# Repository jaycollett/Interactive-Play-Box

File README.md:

# Interactive-Play-Box
Arduino controlled box with buttons, keypads, switches and fun things for kids to poke, push and flip.

Custom Arduino-clone board used to control a box I built for my son for his 4th Christmas.

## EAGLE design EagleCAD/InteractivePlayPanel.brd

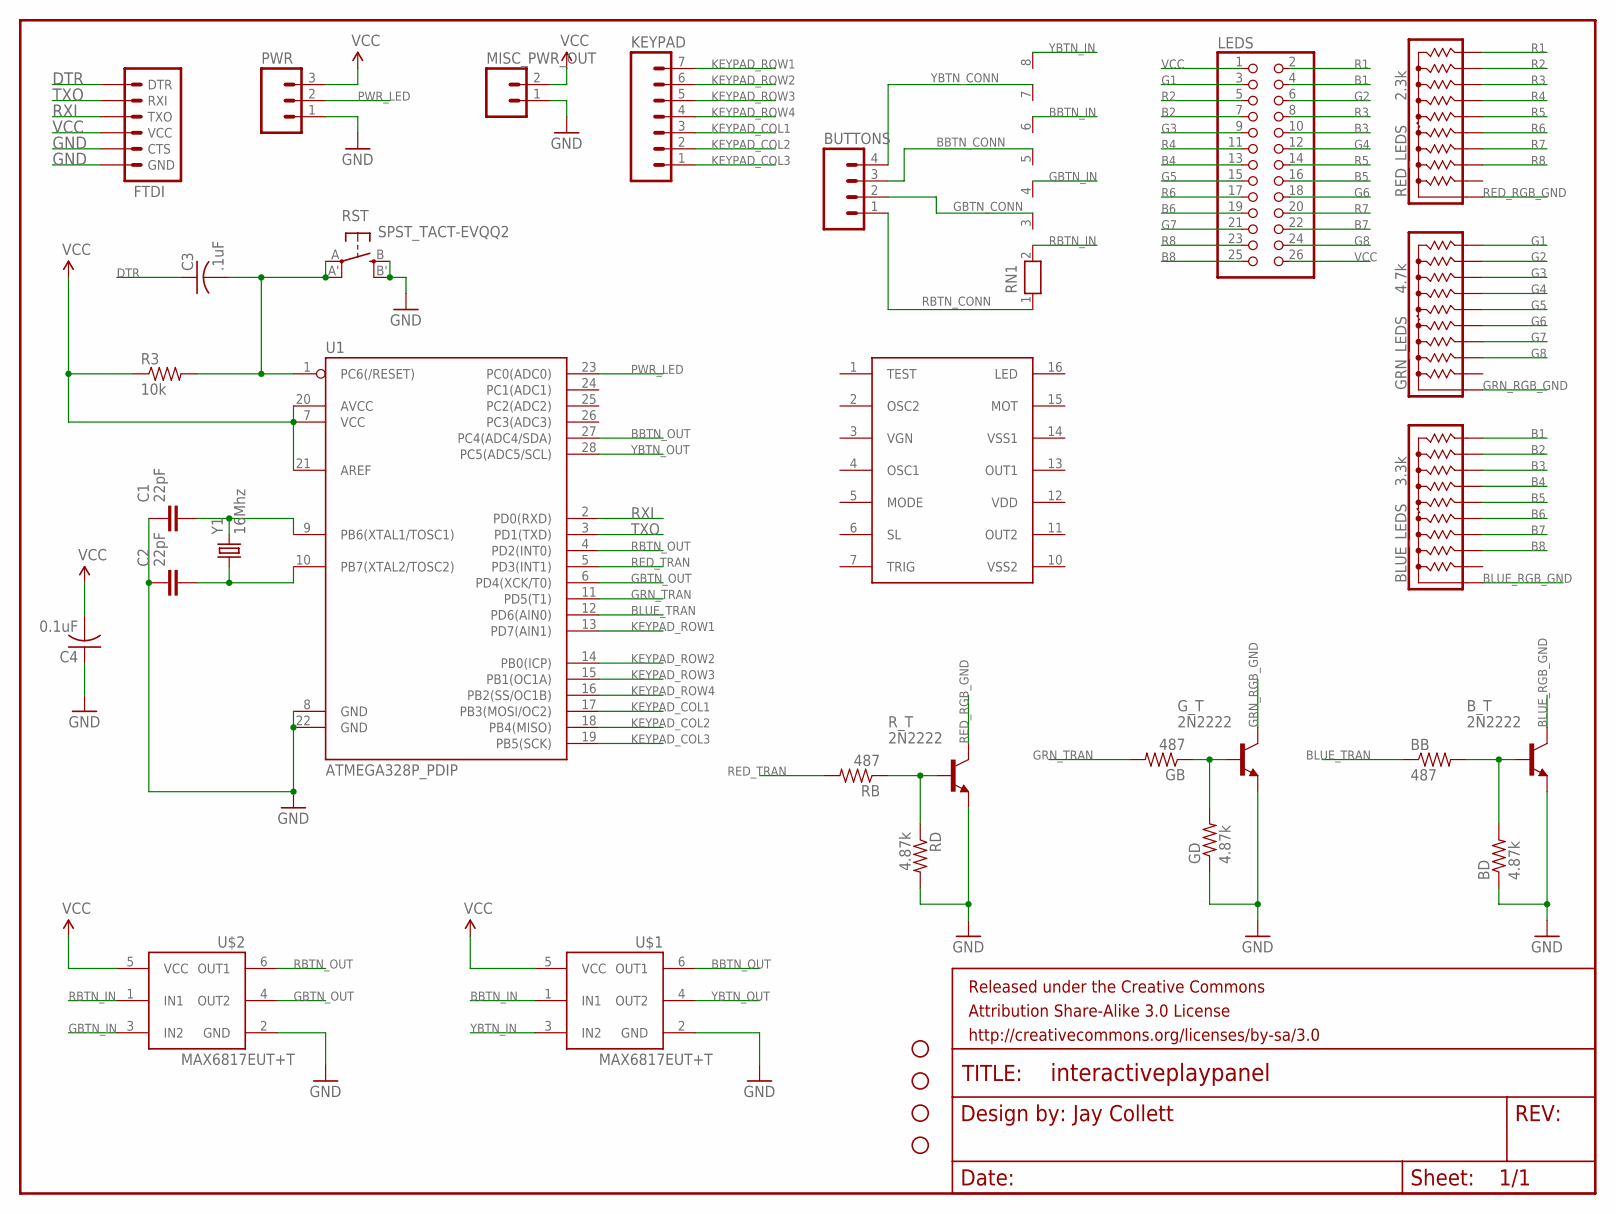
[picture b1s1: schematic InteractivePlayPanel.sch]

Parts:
BB: 487; AXIAL-0.3EZ
BD: 4.87k; AXIAL-0.3EZ
BLUE_LEDS: 3.3k; SIP10
BUTTONS: M04LOCK_LONGPADS; 1X04_LOCK_LONGPADS
B_T: 2N2222; TO92-EBC-OVAL
C1, C2: 22pF; C805
C3: .1uF; C0805
C4: 0.1uF; C0805
FRAME1: FRAME-LETTER; CREATIVE_COMMONS
FTDI: ARDUINO_SERIAL_PROGRAMLOCK; 1X06_LOCK
GB: 487; AXIAL-0.3EZ
GD: 4.87k; AXIAL-0.3EZ
GRN_LEDS: 4.7k; SIP10
G_T: 2N2222; TO92-EBC-OVAL
KEYPAD: M07LOCK_LONGPADS; 1X07_LOCK_LONGPADS
LEDS: PINHD-2X13; 2X13
MISC_PWR_OUT: M02PTH3; 1X02_LONGPADS
PWR: M03LOCK_LONGPADS; 1X03_LOCK_LONGPADS
R3: 10k; 0805
RB: 487; AXIAL-0.3EZ
RD: 4.87k; AXIAL-0.3EZ
RED_LEDS: 2.3k; SIP10
RN1: RN07; RN-8
RST: SPST_TACT-EVQQ2; EVQ-Q2
R_T: 2N2222; TO92-EBC-OVAL
STANDOFF1, STANDOFF2, STANDOFF3, STANDOFF4: STAND-OFF
U1: ATMEGA328P_PDIP; DIL28-3
U$1, U$2: MAX6817EUT+T; SOT-23-6
U$3: HK326-X; DIL16
Y1: 16Mhz; CRYSTAL-SMD-5X3

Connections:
B1: BLUE_LEDS.10, LEDS.4
B2: BLUE_LEDS.9, LEDS.7
B3: BLUE_LEDS.8, LEDS.10
B4: BLUE_LEDS.7, LEDS.13
B5: BLUE_LEDS.6, LEDS.16
B6: BLUE_LEDS.5, LEDS.19
B7: BLUE_LEDS.4, LEDS.22
B8: BLUE_LEDS.3, LEDS.25
BBTN_CONN: BUTTONS.3, RN1.5
BBTN_IN: RN1.6, U$1.1 (IN1)
BBTN_OUT: U1.27 (PC4(ADC4/SDA)), U$1.6 (OUT1)
BLUE_RGB_GND: BLUE_LEDS.1, B_T.C
BLUE_TRAN: BB.P$1 (1), U1.12 (PD6(AIN0))
DTR: C3.1, FTDI.1 (DTR)
G1: GRN_LEDS.10, LEDS.3
G2: GRN_LEDS.9, LEDS.6
G3: GRN_LEDS.8, LEDS.9
G4: GRN_LEDS.7, LEDS.12
G5: GRN_LEDS.6, LEDS.15
G6: GRN_LEDS.5, LEDS.18
G7: GRN_LEDS.4, LEDS.21
G8: GRN_LEDS.3, LEDS.24
GBTN_CONN: BUTTONS.2, RN1.3
GBTN_IN: RN1.4, U$2.3 (IN2)
GBTN_OUT: U1.6 (PD4(XCK/T0)), U$2.4 (OUT2)
GND: BD.P$1 (1), B_T.E, C1.1, C2.1, C4.1, FTDI.5 (CTS), FTDI.6 (GND), GD.P$1 (1), G_T.E, MISC_PWR_OUT.1, PWR.1, RD.P$2 (2), RST.B (S), RST.B' (S1), R_T.E, U1.8 (GND), U1.22 (GND), U$1.2 (GND), U$2.2 (GND)
GRN_RGB_GND: GRN_LEDS.1, G_T.C
GRN_TRAN: GB.P$2 (2), U1.11 (PD5(T1))
KEYPAD_COL1: KEYPAD.3, U1.17 (PB3(MOSI/OC2))
KEYPAD_COL2: KEYPAD.2, U1.18 (PB4(MISO))
KEYPAD_COL3: KEYPAD.1, U1.19 (PB5(SCK))
KEYPAD_ROW1: KEYPAD.7, U1.13 (PD7(AIN1))
KEYPAD_ROW2: KEYPAD.6, U1.14 (PB0(ICP))
KEYPAD_ROW3: KEYPAD.5, U1.15 (PB1(OC1A))
KEYPAD_ROW4: KEYPAD.4, U1.16 (PB2(SS/OC1B))
unnamed: C1.2, U1.9 (PB6(XTAL1/TOSC1)), Y1.3 (2)
unnamed: C2.2, U1.10 (PB7(XTAL2/TOSC2)), Y1.1
unnamed: RB.P$1 (1), RD.P$1 (1), R_T.B
unnamed: GB.P$1 (1), GD.P$2 (2), G_T.B
unnamed: BB.P$2 (2), BD.P$2 (2), B_T.B
PWR_LED: PWR.2, U1.23 (PC0(ADC0))
R1: LEDS.2, RED_LEDS.10
R2: LEDS.5, RED_LEDS.9
R3: LEDS.8, RED_LEDS.8
R4: LEDS.11, RED_LEDS.7
R5: LEDS.14, RED_LEDS.6
R6: LEDS.17, RED_LEDS.5
R7: LEDS.20, RED_LEDS.4
R8: LEDS.23, RED_LEDS.3
RBTN_CONN: BUTTONS.1, RN1.1
RBTN_IN: RN1.2, U$2.1 (IN1)
RBTN_OUT: U1.4 (PD2(INT0)), U$2.6 (OUT1)
RED_RGB_GND: RED_LEDS.1, R_T.C
RED_TRAN: RB.P$2 (2), U1.5 (PD3(INT1))
RST: C3.2, R3.2, RST.A, RST.A' (P1), U1.1 (PC6(/RESET))
RXI: FTDI.3 (TXO), U1.2 (PD0(RXD))
TXO: FTDI.2 (RXI), U1.3 (PD1(TXD))
VCC: C4.2, FTDI.4 (VCC), LEDS.1, LEDS.26, MISC_PWR_OUT.2, PWR.3, R3.1, U1.7 (VCC), U1.20 (AVCC), U1.21 (AREF), U$1.5 (VCC), U$2.5 (VCC)
YBTN_CONN: BUTTONS.4, RN1.7
YBTN_IN: RN1.8, U$1.3 (IN2)
YBTN_OUT: U1.28 (PC5(ADC5/SCL)), U$1.4 (OUT2)

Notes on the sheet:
Jay Collett

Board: 2 copper layers, 35 parts (0 on the bottom side), 61 nets, no tracks yet.

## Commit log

2018-02-09 Adding project to GitHub
2018-02-09 Create LICENSE

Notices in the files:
parts and their libraries:
SparkFun-Aesthetics: Licensing: CC v3.0 Share-Alike You are welcome to use this library for commercial purposes.
SparkFun-Aesthetics: Released under the Creative Commons Attribution Share-Alike 3.0 License
SparkFun-Aesthetics: http://creativecommons.org/licenses/by-sa/3.0
